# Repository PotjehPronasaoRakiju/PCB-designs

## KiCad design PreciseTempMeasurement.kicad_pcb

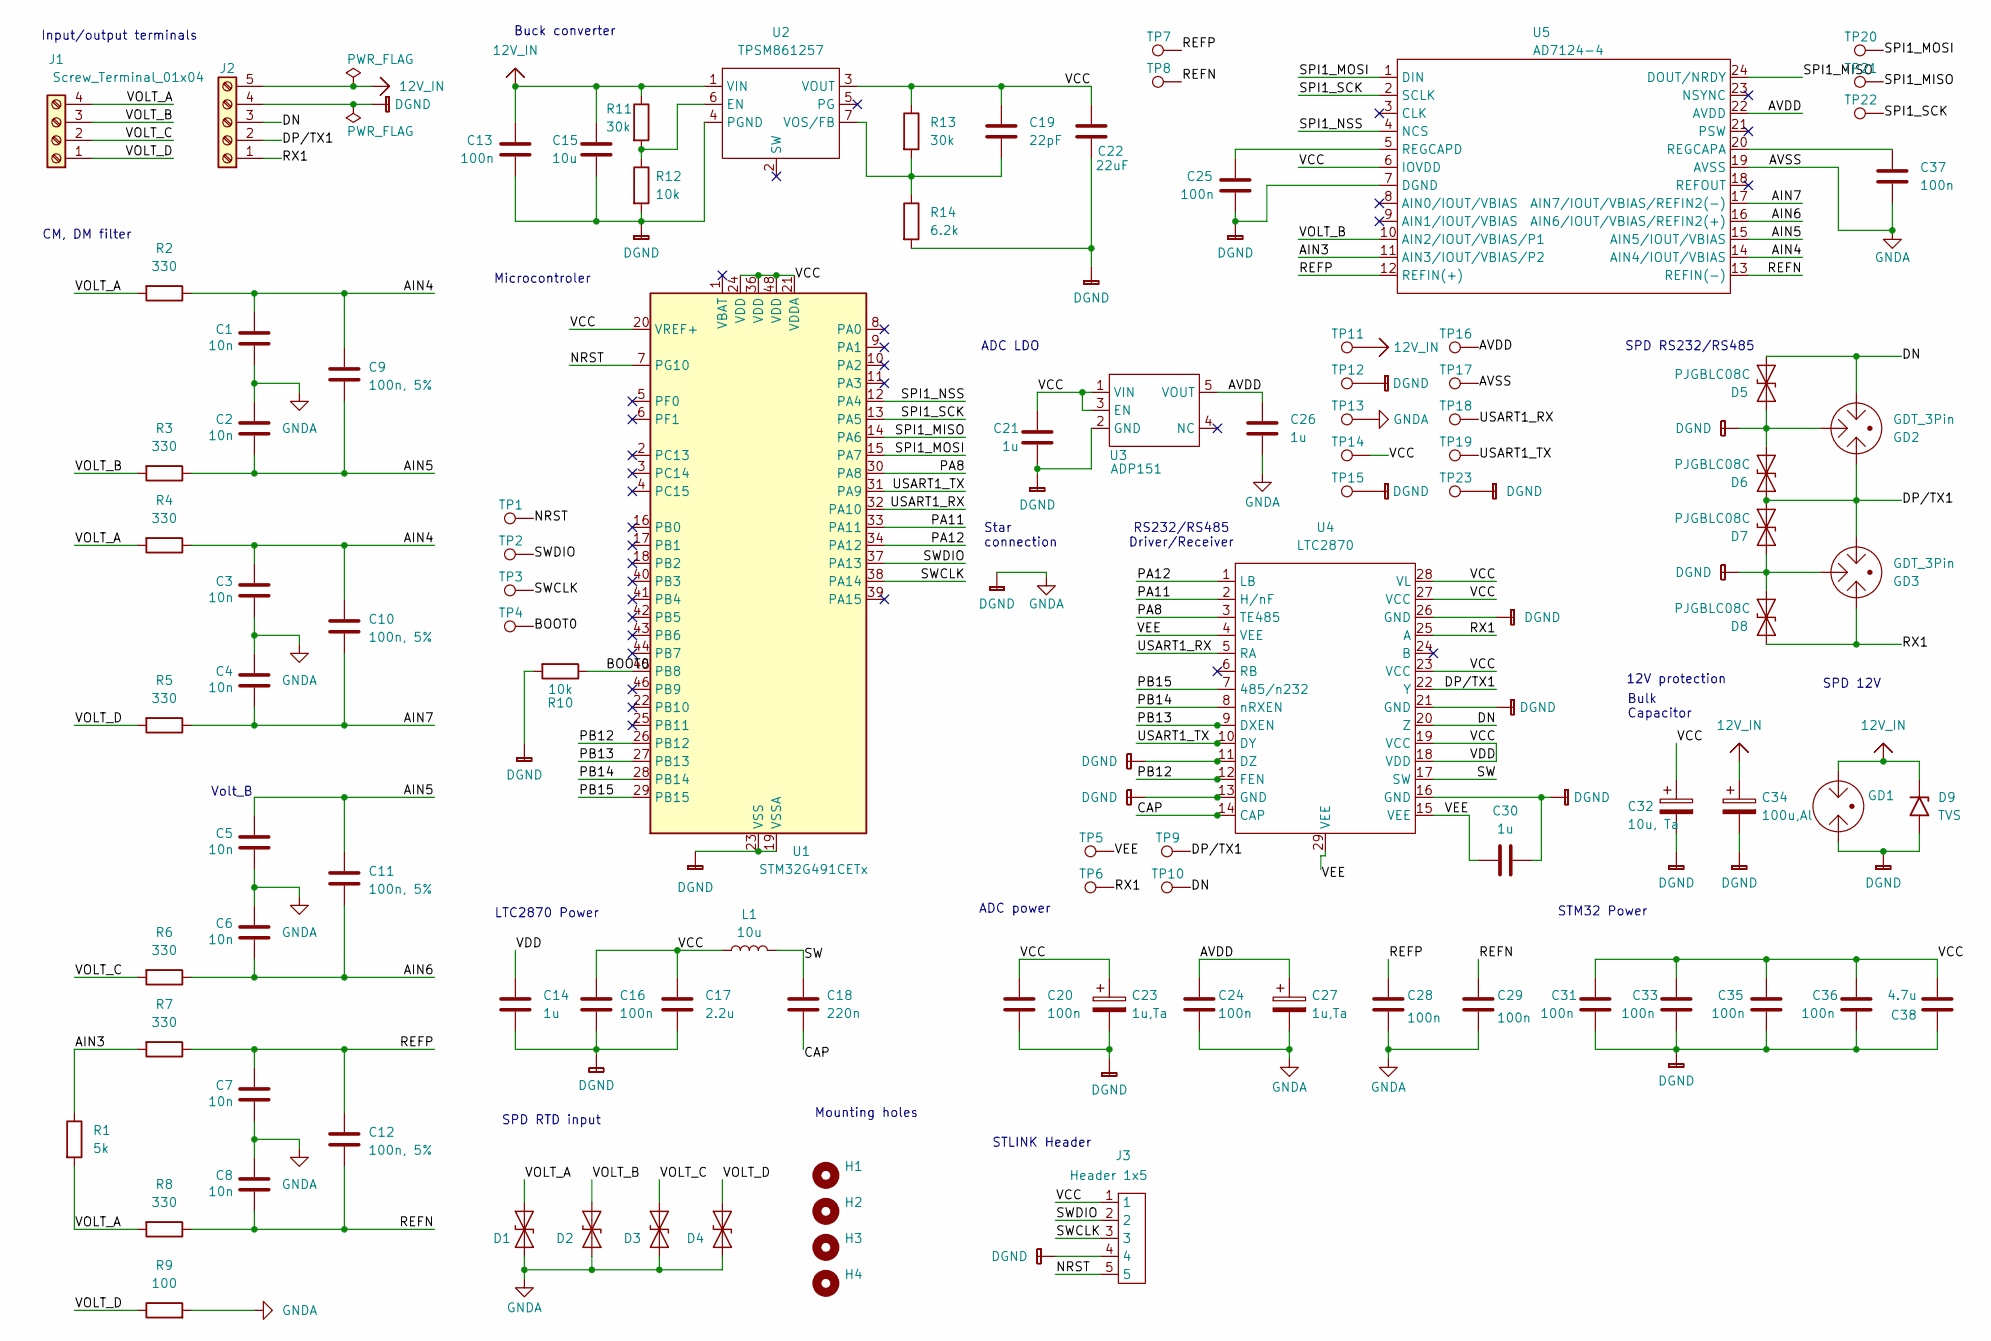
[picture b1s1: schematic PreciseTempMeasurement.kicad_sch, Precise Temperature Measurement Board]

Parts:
C1, C2, C3, C4, C5, C6, C7, C8: 10n; 0805; Part no. 581-08051C103J4Z2A
C9, C10, C11, C12: 100n, 5%; 0805; Part no. 77-VJ0805Y104JXARBC
C13, C16, C20, C24, C25, C28, C29, C31, C33, C35, C36, C37: 100n; 0603; Part no. 603-CC603KRX5R9BB104
C14, C21, C26, C30: 1u; 0805; Part no. 791-0805X105K250CT
C15: 10u; 1206; Part no. 963-TMK316BJ106KL-T
C17: 2.2u; 0805; Part no. 603-CC805KRX5R7BB225
C18: 220n; 0805; Part no. 603-CC805KRX7R8BB224
C19: 22pF; 0805; Part no. 77-VJ0805A220KXAMC
C22: 22uF; 1206; Part no. 581-KGM31AR70J226KU
C23, C27: 1u,Ta; 0603_pol; Part no. 74-TMCJ1C105MTRF
C32: 10u, Ta; 0805; Part no. 74-293D106X0010A2TE3
C34: 100u,Al; Radial; Part no. 232-25YXM100MEFR63X1
C38: 4.7u; 0805; Part no. 187-CL21A475KAQNNNE
D1, D2, D3, D4: ESDL2012MX4T5G; X4DFN-2; Part no. 863-ESDL2012MX4T5G
D5, D6, D7, D8: PJGBLC08C; SOD23; Part no. 241-PJGBLC08CR100001
D9: TVS; DFN-1610-2; Part no. 445-SY205245SLC
GD1: 2049-23; GDT 2 pin; Part no. 652-2049-23-BLF
GD2, GD3: GDT_3Pin; GDT 3 pin; Part no. 652-2046-23-C2LF
H1, H2, H3, H4: MountingHole; Hole 0.125 inch 3.175 mm
J1: Screw_Terminal_01x04; Terminal 1x4; Part no. 710-691244510004
J2: Screw_Terminal_01x05; Terminal 1x5; Part no. 710-691244510005
J3: Header 1x5; Part no. 649-77311-122-05LF
L1: 10u; 0806; Part no. 963-LBC2016T100K
R1: 5k; Resistor_THT; Part no. 71-Z201T5K0000VB
R2, R3, R4, R5, R6, R7, R8: 330; 0805; Part no. 756-WCR0805-330RFI
R9: 100; 0603; Part no. 71-CRCW0603100RFKECC
R10, R12: 10k; 0805; Part no. 603-SR0805KR-0710KL
R11, R13: 30k; 0805; Part no. 603-RT0805DRD0730KL
R14: 6.2k; 0805; Part no. 754-RR1220P-622D
TP1, TP2, TP3, TP4, TP5, TP6, TP7, TP8, TP9, TP10, TP11, TP12, TP13, TP14, TP15, TP16, TP17, TP18, TP19, TP20, TP21, TP22, TP23: TestPoint; Testpoint
U1: STM32G491CETx; QFP50P900X900X160-48N; Part no. 511-STM32G491CET6
U2: TPSM861257; VREG_TPSM861253RDXR; Part no. 595-TPSM861257RDXR
U3: ADP151; UJ_5_ADI; Part no. 584-ADP151AUJZ-3.3R7
U4: LTC2870; TSSOP-28_FE&slash_EB_LIT; Part no. 584-LTC2870IFE#TRPBF
U5: AD7124-4; SOP65P640X120-24N; Part no. 584-AD7124-4BRUZ

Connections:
12V_IN: C13.1, C15.1, C34.1, D9.1 (A1), GD1.3, J2.5, R11.1, TP11.1, U2.1 (VIN)
/AIN3: R1.1, R7.2, U5.11 (AIN3/IOUT/VBIAS/P2)
/AIN4: C1.1, C3.1, C9.1, C10.1, R2.1, R4.1, U5.14 (AIN4/IOUT/VBIAS)
/AIN5: C2.2, C5.1, C9.2, C11.1, R3.1, U5.15 (AIN5/IOUT/VBIAS)
/AIN6: C6.2, C11.2, R6.1, U5.16 (AIN6/IOUT/VBIAS/REFIN2(+))
/AIN7: C4.2, C10.2, R5.1, U5.17 (AIN7/IOUT/VBIAS/REFIN2(-))
/AVDD: C24.1, C26.1, C27.1, TP16.1, U3.5 (VOUT), U5.22 (AVDD)
/BOOT0: R10.1, TP4.1, U1.45 (PB8)
/CAP: C18.2, U4.14 (CAP)
/DN: D5.1 (A1), GD2.3, J2.3, TP10.1, U4.20 (Z)
/DP/TX1: D6.2 (A2), D7.1 (A1), GD2.1, GD3.3, J2.2, TP9.1, U4.22 (Y)
/NRST: J3.5, TP1.1, U1.7 (PG10)
/PA8: U1.30 (PA8), U4.3 (TE485)
/PA11: U1.33 (PA11), U4.2 (H/nF)
/PA12: U1.34 (PA12), U4.1 (LB)
/PB12: U1.26 (PB12), U4.12 (FEN)
/PB13: U1.27 (PB13), U4.9 (DXEN)
/PB14: U1.28 (PB14), U4.8 (nRXEN)
/PB15: U1.29 (PB15), U4.7 (485/n232)
/REFN: C8.2, C12.2, C29.1, R8.1, TP8.1, U5.13 (REFIN(-))
/REFP: C7.1, C12.1, C28.1, R7.1, TP7.1, U5.12 (REFIN(+))
/RX1: D8.2 (A2), GD3.1, J2.1, TP6.1, U4.25 (A)
/SPI1_MISO: TP21.1, U1.14 (PA6), U5.24 (DOUT/NRDY)
/SPI1_MOSI: TP20.1, U1.15 (PA7), U5.1 (DIN)
/SPI1_NSS: U1.12 (PA4), U5.4 (NCS)
/SPI1_SCK: TP22.1, U1.13 (PA5), U5.2 (SCLK)
/SW: C18.1, L1.2, U4.17 (SW)
/SWCLK: J3.3, TP3.1, U1.38 (PA14)
/SWDIO: J3.2, TP2.1, U1.37 (PA13)
/USART1_RX: TP18.1, U1.32 (PA10), U4.5 (RA)
/USART1_TX: TP19.1, U1.31 (PA9), U4.10 (DY)
/VCC: C14.1, C16.1, C17.1, C19.1, C20.1, C21.1, C22.1, C23.1, C31.1, C32.1, C33.1, C35.1, C36.1, C38.2, J3.1, L1.1, R13.1, TP14.1, U1.20 (VREF+), U1.21 (VDDA), U1.24 (VDD), U1.36 (VDD), U1.48 (VDD), U2.3 (VOUT), U2.14, U2.15, U2.16, U2.17, U2.18, U2.19, U3.1 (VIN), U3.3 (EN), U4.18 (VDD), U4.19 (VCC), U4.23 (VCC), U4.27 (VCC), U4.28 (VL), U5.6 (IOVDD)
/VEE: C30.1, TP5.1, U4.4 (VEE), U4.15 (VEE), U4.29 (VEE)
/VOLT_A: D1.1 (A1), J1.4, R1.2, R2.2, R4.2, R8.2
/VOLT_B: D2.1 (A1), J1.3, R3.2, U5.10 (AIN2/IOUT/VBIAS/P1)
/VOLT_C: D3.1 (A1), J1.2, R6.2
/VOLT_D: D4.1 (A1), J1.1, R5.2, R9.1
DGND: C1.2, C2.1, C3.2, C4.1, C5.2, C6.1, C7.2, C8.1, C13.2, C14.2, C15.2, C16.2, C17.2, C20.2, C21.2, C22.2, C23.2, C24.2, C25.2, C26.2, C27.2, C28.2, C29.2, C30.2, C31.2, C32.2, C33.2, C34.2, C35.2, C36.2, C37.2, C38.1, D1.2 (A2), D2.2 (A2), D3.2 (A2), D4.2 (A2), D5.2 (A2), D6.1 (A1), D7.2 (A2), D8.1 (A1), D9.2 (A2), GD1.1, GD2.2, GD3.2, J2.4, J3.4, R9.2, R10.2, R12.2, R14.2, TP12.1, TP13.1, TP15.1, TP17.1, TP23.1, U1.19 (VSSA), U1.23 (VSS), U1.35 (VSS), U1.47 (VSS), U2.4 (PGND), U3.2 (GND), U4.11 (DZ), U4.13 (GND), U4.16 (GND), U4.21 (GND), U4.26 (GND), U5.7 (DGND), U5.19 (AVSS)
unnamed: R11.2, R12.1, U2.6 (EN)
unnamed: C19.2, R13.2, R14.1, U2.7 (VOS/FB)
unnamed: C37.1, U5.20 (REGCAPA)
unnamed: C25.1, U5.5 (REGCAPD)

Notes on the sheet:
Microcontroler
SPD 12V
CM, DM filter
Buck converter
Star connection
SPD RTD input
Mounting holes
RS232/RS485 Driver/Receiver
STLINK Header
Input/output terminals
LTC2870 Power
ADC LDO
SPD RS232/RS485
STM32 Power
ADC power
Bulk Capacitor
12V protection
Volt_B

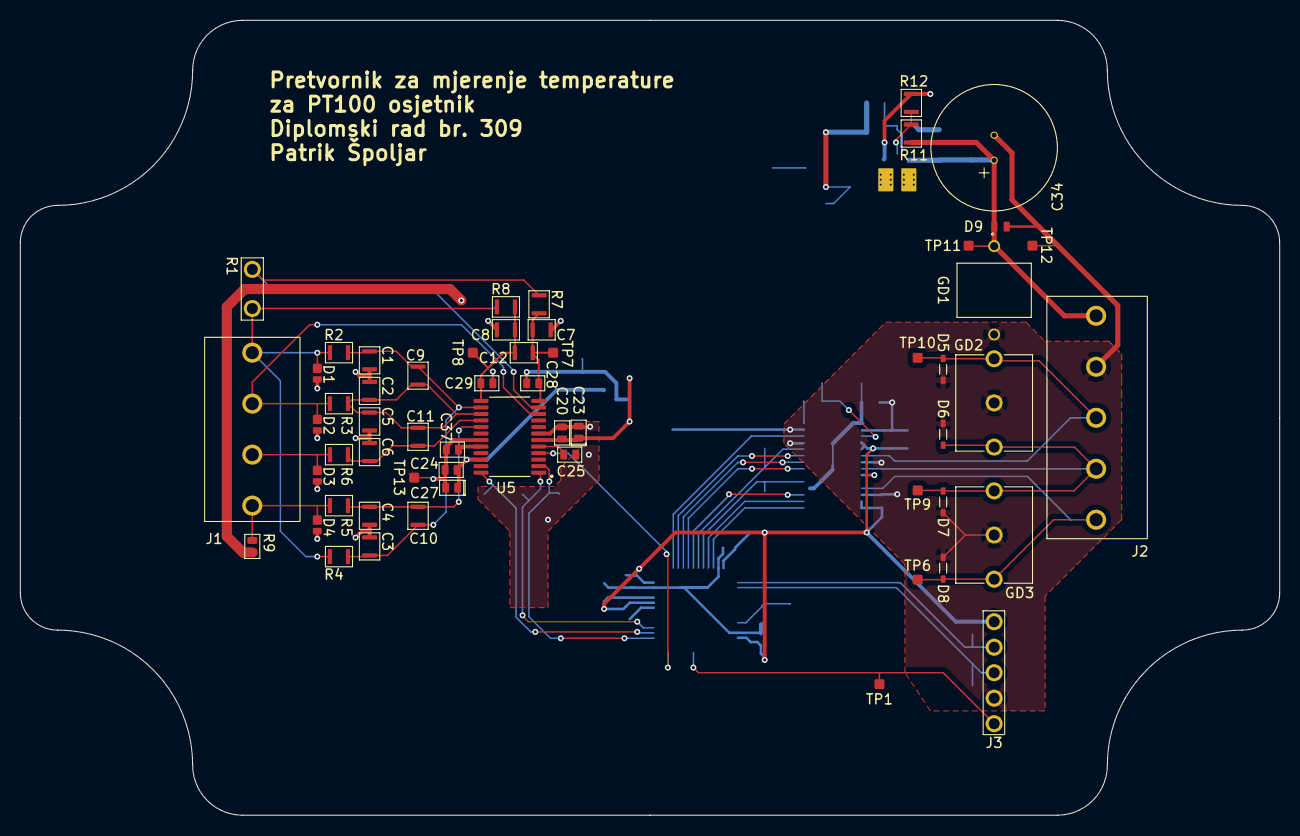
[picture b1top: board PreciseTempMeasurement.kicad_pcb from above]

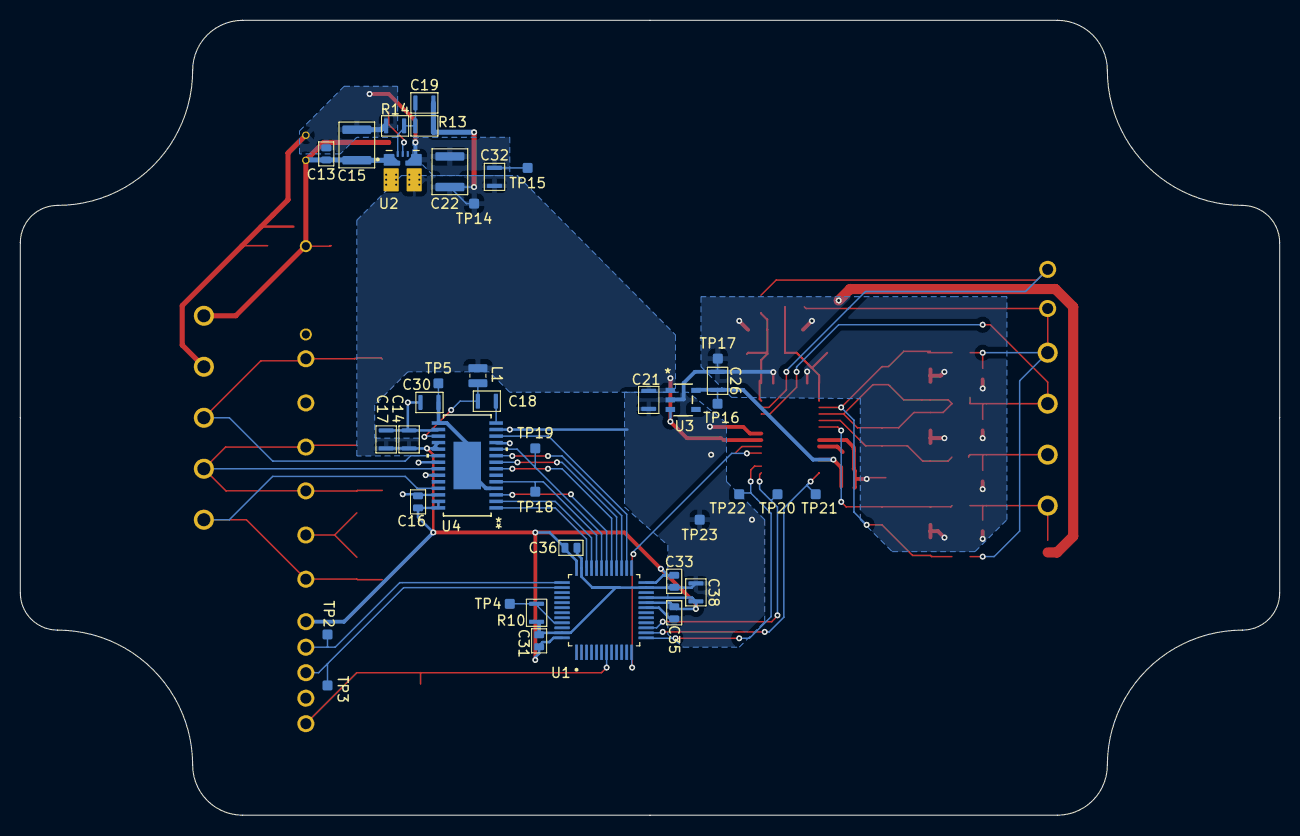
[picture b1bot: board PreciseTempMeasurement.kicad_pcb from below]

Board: 2 copper layers, 125.5 x 79.2 mm, 100 parts (39 on the bottom side), 42 nets.

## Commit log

2026-02-01 Rev A: initial PCB Design
2026-02-01 Delete PreciseTempMeasurement-backups directory
    because of .gitignore error
2026-02-01 Delete ~PreciseTempMeasurement.kicad_sch.lck
    .gitignore error
2026-02-01 Delete PreciseTempMeasurement.zip
    .gitignore error
